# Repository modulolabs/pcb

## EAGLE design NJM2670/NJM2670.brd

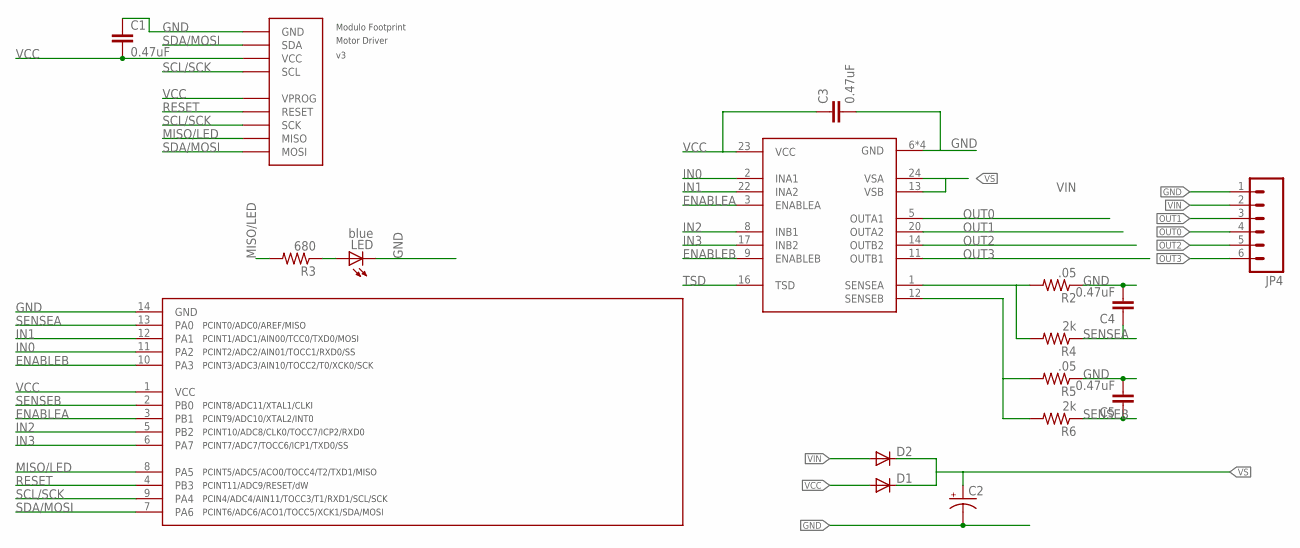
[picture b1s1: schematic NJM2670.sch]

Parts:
C1, C3, C4, C5: 0.47uF; 0805
C2: CAP_POLC; PANASONIC_C
D1, D2: DIODESMA; SMA-DIODE
JP4: M063.5MM-6; SCREWTERMINAL-3.5MM-6
LED: blue; CHIPLED_0805
R2, R5: .05; 0805
R3: 680; 0805
R4, R6: 2k; 0805
U$1: FOOTPRINTFOOTPRINT-2; FOOTPRINT2
U$3: TINY841; SOIC14
U$6: NJM2670; SOP-24-E3

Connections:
ENABLEA: U$3.3 (PB1), U$6.3 (ENABLEA)
ENABLEB: U$3.10 (PA3), U$6.9 (ENABLEB)
GND: C1.1, C2.-, C3.2, C4.2, C5.2, JP4.1, LED.C, R2.1, R5.1, U$1.BUS0 (GND), U$3.14 (GND), U$6.6 (GND), U$6.7 (GND), U$6.18 (GND), U$6.19 (GND)
IN0: U$3.11 (PA2), U$6.2 (INA1)
IN1: U$3.12 (PA1), U$6.22 (INA2)
IN2: U$3.5 (PB2), U$6.8 (INB1)
IN3: U$3.6 (PA7), U$6.17 (INB2)
MISO/LED: R3.2, U$1.PROG3 (MISO), U$3.8 (PA5)
unnamed: R2.2, R4.2, U$6.1 (SENSEA)
unnamed: R5.2, R6.2, U$6.12 (SENSEB)
unnamed: LED.A, R3.1
OUT0: JP4.4, U$6.5 (OUTA1)
OUT1: JP4.3, U$6.20 (OUTA2)
OUT2: JP4.5, U$6.14 (OUTB2)
OUT3: JP4.6, U$6.11 (OUTB1)
RESET: U$1.PROG1 (RESET), U$3.4 (PB3)
SCL/SCK: U$1.BUS3 (SCL), U$1.PROG2 (SCK), U$3.9 (PA4)
SDA/MOSI: U$1.BUS1 (SDA), U$1.PROG4 (MOSI), U$3.7 (PA6)
SENSEA: C4.1, R4.1, U$3.13 (PA0)
SENSEB: C5.1, R6.1, U$3.2 (PB0)
TSD: U$6.16 (TSD)
VCC: C1.2, C3.1, D1.A, U$1.BUS2 (VCC), U$1.PROG0 (VPROG), U$3.1 (VCC), U$6.23 (VCC)
VIN: D2.A, JP4.2
VS: C2.+, D1.C, D2.C, U$6.13 (VSB), U$6.24 (VSA)

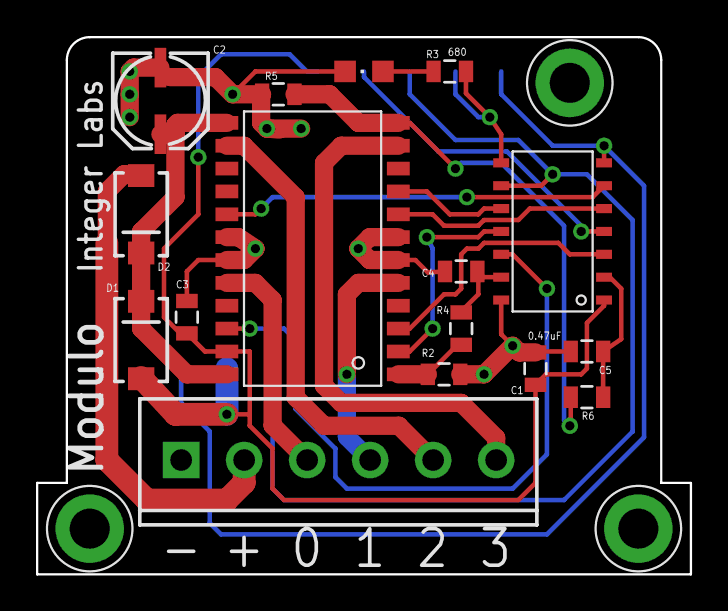
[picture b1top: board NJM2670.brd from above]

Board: 2 copper layers, 36.3 x 29.8 mm, 17 parts (0 on the bottom side), 23 nets.

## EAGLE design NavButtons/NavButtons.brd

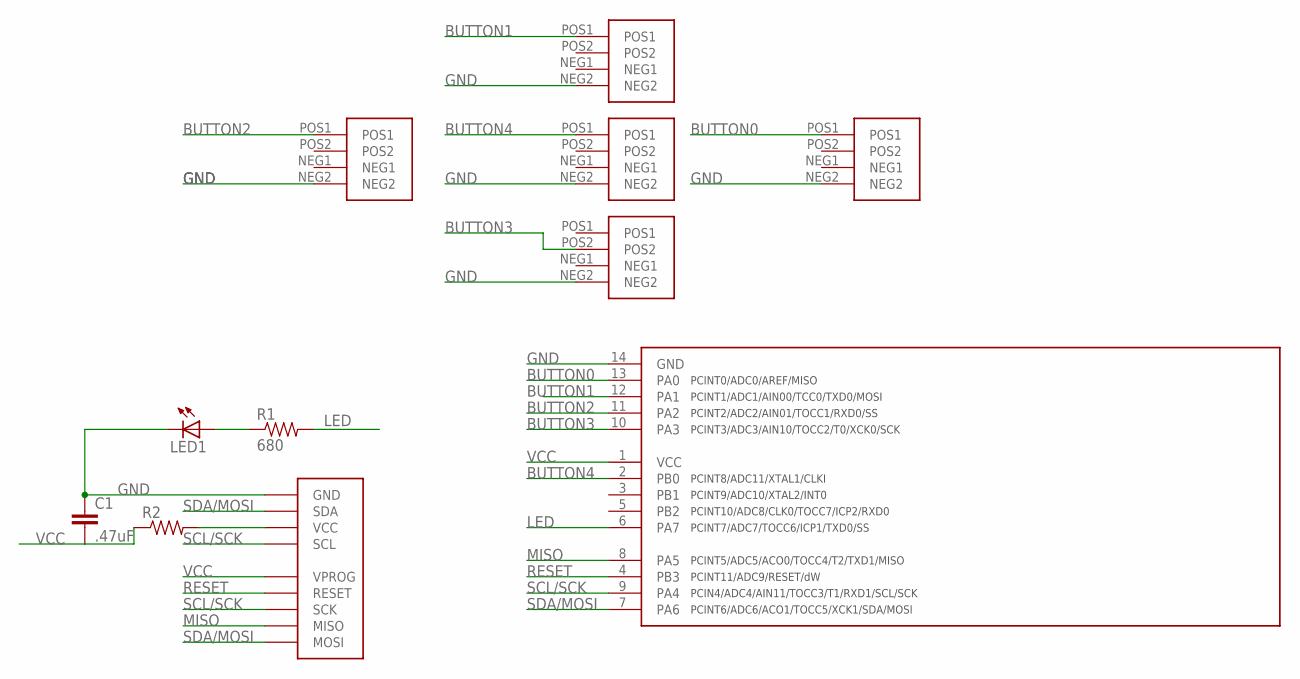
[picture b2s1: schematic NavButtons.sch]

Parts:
B1, B3, B4, B5, B7: TACT-SWITCH; MJTP1138
C1: .47uF; 0805
LED1: LEDCHIP-LED0805; CHIP-LED0805
R1: 680; 0805
R2: RESISTOR0805-RES; 0805
U$1: TINY841; SOIC14
U$2: FOOTPRINTFOOTPRINT-2; FOOTPRINT2

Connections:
BUTTON0: B5.POS1, U$1.13 (PA0)
BUTTON1: B1.POS1, U$1.12 (PA1)
BUTTON2: B3.POS1, U$1.11 (PA2)
BUTTON3: B7.POS2, U$1.10 (PA3)
BUTTON4: B4.POS1, U$1.2 (PB0)
GND: B1.NEG2, B3.NEG2, B4.NEG2, B5.NEG2, B7.NEG2, C1.1, LED1.C, U$1.14 (GND), U$2.BUS0 (GND)
LED: R1.2, U$1.6 (PA7)
MISO: U$1.8 (PA5), U$2.PROG3 (MISO)
unnamed: R2.2, U$2.BUS2 (VCC)
unnamed: LED1.A, R1.1
RESET: U$1.4 (PB3), U$2.PROG1 (RESET)
SCL/SCK: U$1.9 (PA4), U$2.BUS3 (SCL), U$2.PROG2 (SCK)
SDA/MOSI: U$1.7 (PA6), U$2.BUS1 (SDA), U$2.PROG4 (MOSI)
VCC: C1.2, R2.1, U$1.1 (VCC), U$2.PROG0 (VPROG)

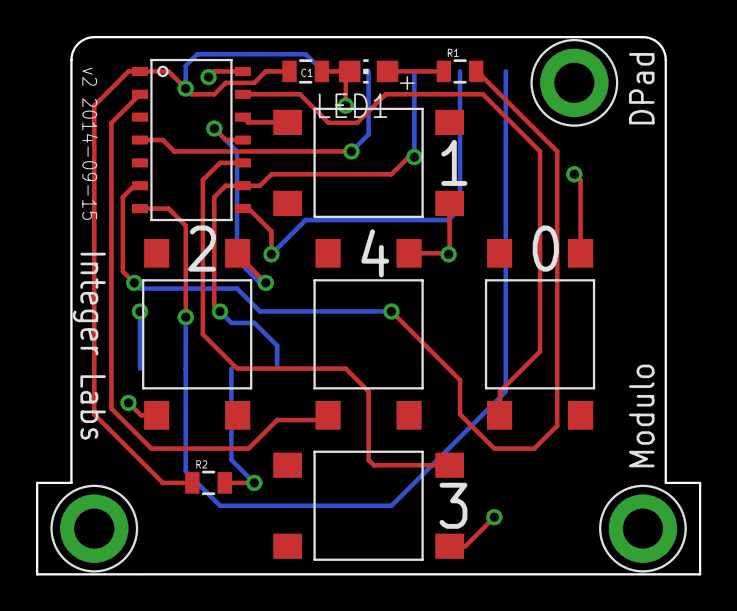
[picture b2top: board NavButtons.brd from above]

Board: 2 copper layers, 36.8 x 29.8 mm, 11 parts (0 on the bottom side), 14 nets.

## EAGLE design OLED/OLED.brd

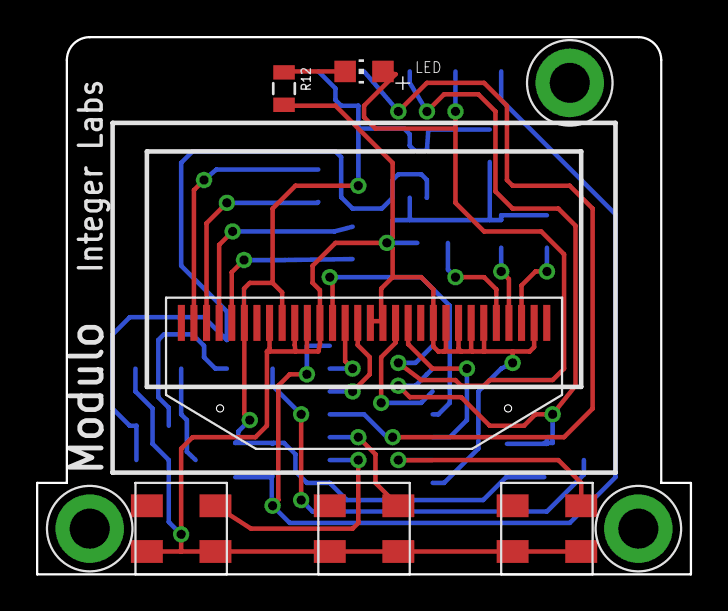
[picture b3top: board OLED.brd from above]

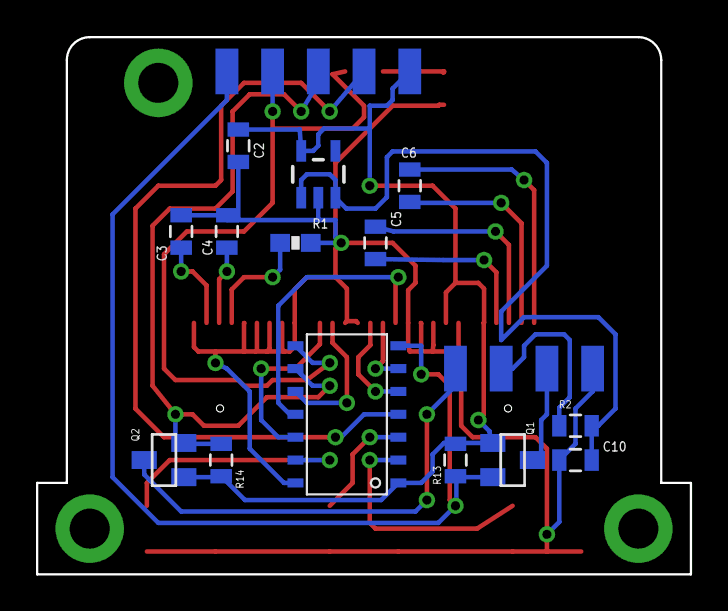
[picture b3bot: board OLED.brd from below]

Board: 2 copper layers, 36.3 x 29.8 mm, 21 parts (14 on the bottom side), 26 nets.

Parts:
C2, C10: .47uF; 0805
C3, C4: 2.2uF; 0805
C5, C6: 1uF; 0805
LED: blue; CHIP-LED0805
Q1, Q2: MOSFET-NCHANNELBSS138; SOT23
R1: 390k; 0603-RES
R2: 1; 0805
R12: 680; 0805
R13, R14: 2k; 0805
U$1: OLEDREVERSE; FPC-30-REVERSE
U$2: 3.3V/150mA; SOT23-5
U$3: TINY841; SOIC14
U$4: FOOTPRINTFOOTPRINT-2; FOOTPRINT2
U$5, U$6, U$7: TACT-SWITCHBOURNS-7914J; BOURNS-7914J

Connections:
+3.3V: C2.2, Q1.1, Q2.1, R13.2, R14.2, U$1.6, U$1.9, U$2.5, U$3.1, U$4.PROG0
+5V: C10.2, R2.1, U$2.1, U$2.3
BUTTON1: U$3.2, U$5.POS$1
BUTTON2: U$3.3, U$6.POS$1
BUTTON3: U$3.13, U$7.POS$1
DISPLAY_CS: U$1.13, U$3.11
DISPLAY_D/C: U$1.15, U$3.5
DISPLAY_MOSI: U$1.19, U$3.12
DISPLAY_RESET: U$1.14, U$3.6
DISPLAY_SCK: U$1.18, U$3.10
GND: C2.1, C3.2, C4.2, C10.1, R1.1, R12.1, U$1.8, U$1.10, U$1.11, U$1.12, U$1.16, U$1.17, U$1.21, U$1.22, U$1.23, U$1.24, U$1.25, U$1.29, U$2.2, U$3.14, U$4.BUS0, U$5.NEG$1, U$5.NEG$2, U$6.NEG$1, U$6.NEG$2, U$7.NEG$1, U$7.NEG$2
MISO/LED: LED.A, U$3.8, U$4.PROG3
unnamed: R1.2, U$1.26
unnamed: R2.2, U$4.BUS2
unnamed: C3.1, U$1.28
unnamed: C4.1, U$1.27
unnamed: LED.C, R12.2
unnamed: C5.2, U$1.4
unnamed: C6.2, U$1.2
unnamed: C5.1, U$1.5
unnamed: C6.1, U$1.3
RESET: U$3.4, U$4.PROG1
SCL3.3/SCK: Q2.2, R14.1, U$3.9, U$4.PROG2
SCL5: Q2.3, U$4.BUS3
SDA3.3/MOSI: Q1.2, R13.1, U$3.7, U$4.PROG4
SDA5: Q1.3, U$4.BUS1

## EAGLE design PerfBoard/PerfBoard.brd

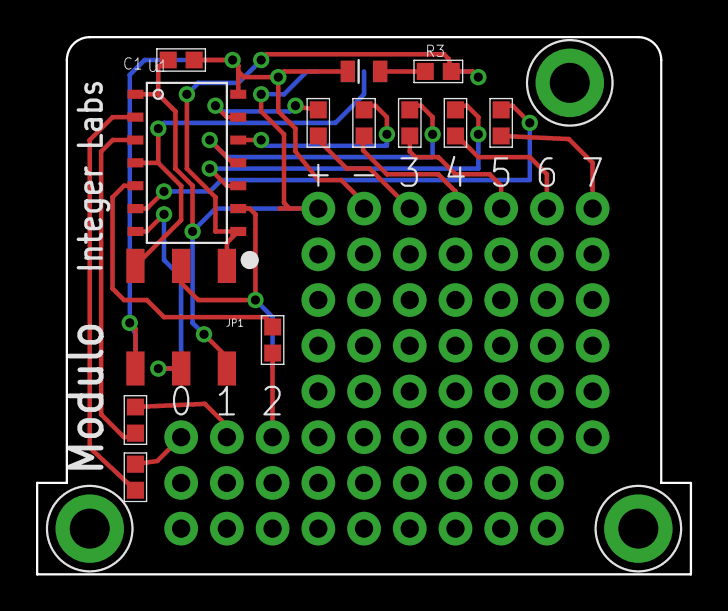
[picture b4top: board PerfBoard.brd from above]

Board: 2 copper layers, 36.3 x 29.8 mm, 31 parts (0 on the bottom side), 23 nets.

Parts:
C1: 100nF; 0603
JP1: 2X3_SMD
JP2, JP5, JP8, JP9, JP12, JP13: 1X05_NO_SILK
JP3, JP4, JP6, JP7, JP10, JP11, JP14, JP15, JP16, JP17, JP18: 1X03_NO_SILK
LED1: blue; 0805-LED
PCB1: EXCLUDE; FOOTPRINT2
R1, R2, R4, R5, R6, R7, R8, R9: 150Ω; 0603
R3: 681Ω; 0603
U1: ATTINY841; SOIC-14

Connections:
A0: R4.1, U1.13
A1: R6.1, U1.12
A2: R8.1, U1.11
A3: R5.1, U1.10
A7: R7.1, U1.6
B0: R9.1, U1.2
B1: R2.1, U1.3
B2: R1.1, U1.5
GND: C1.1, JP1.6, JP7.1, LED1.C, PCB1.BUS0, U1.14
LED/MISO: JP1.1, PCB1.PROG3, R3.2, U1.8
unnamed: LED1.A, R3.1
unnamed: JP3.1, R1.2
unnamed: JP6.1, R2.2
unnamed: JP10.1, R4.2
unnamed: JP11.1, R5.2
unnamed: JP15.1, R7.2
unnamed: JP14.1, R6.2
unnamed: JP16.1, R8.2
unnamed: JP17.1, R9.2
RESET: JP1.5, PCB1.PROG1, U1.4
SCL/SCK: JP1.3, PCB1.BUS3, U1.9
SDA/MOSI: JP1.4, PCB1.BUS1, U1.7
VCC: C1.2, JP1.2, JP4.1, PCB1.BUS2, PCB1.PROG0, U1.1

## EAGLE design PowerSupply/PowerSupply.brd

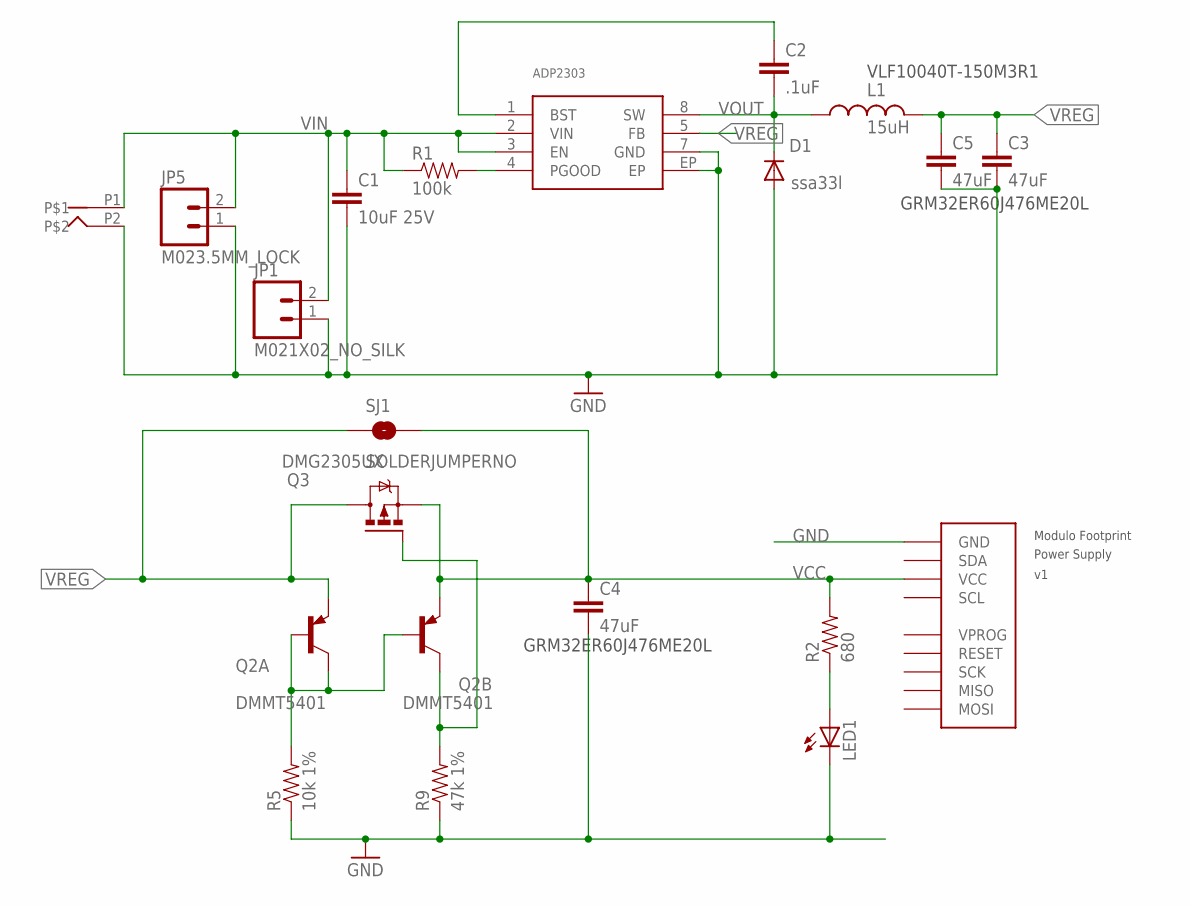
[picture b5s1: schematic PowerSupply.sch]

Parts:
C1: 10uF 25V; 0805
C2: .1uF; 0805
C3, C4, C5: 47uF; 1210
D1: ssa33l; SMA-DIODE
JP1: M021X02_NO_SILK; 1X02_NO_SILK
JP5: M023.5MM_LOCK; SCREWTERMINAL-3.5MM-2_LOCK
L1: 15uH; INDUCTOR-VLF10040
LED1: LEDCHIPLED_0805; CHIPLED_0805
Q2: DMMT5401; SOT-26
Q3: DMG2305UX; MICRO3
R1: 100k; 0805
R2: 680; 0805
R5: 10k 1%; 0805
R9: 47k 1%; 0805
SJ1: SOLDERJUMPERNO; SJ_2S-NO
U$3: ADP2303; SOIC8-EP
U$4: FOOTPRINTFOOTPRINT-2; FOOTPRINT2
U$21: DC-JACK; DC-POWER-JACK

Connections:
GND: C1.2, C3.2, C4.2, C5.2, D1.A, JP1.1, JP5.1, LED1.C, R5.1, R9.1, U$3.7 (GND), U$3.EP, U$4.BUS0 (GND), U$21.P2
unnamed: R1.2, U$3.4 (PGOOD)
unnamed: LED1.A, R2.1
unnamed: C2.1, U$3.1 (BST)
unnamed: Q2.1 (C), Q2.2 (B), Q2.3 (B), R5.2
unnamed: Q2.4 (C), Q3.1 (G), R9.2
VCC: C4.1, Q2.5 (E), Q3.2 (S), R2.2, SJ1.2, U$4.BUS2 (VCC)
VIN: C1.1, JP1.2, JP5.2, R1.1, U$3.2 (VIN), U$3.3 (EN), U$21.P1
VOUT: C2.2, D1.C, L1.P$1 (1), U$3.8 (SW)
VREG: C3.1, C5.1, L1.P$2 (2), Q2.6 (E), Q3.3 (D), SJ1.1, U$3.5 (FB)

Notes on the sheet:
GRM32ER60J476ME20L
VLF10040T-150M3R1

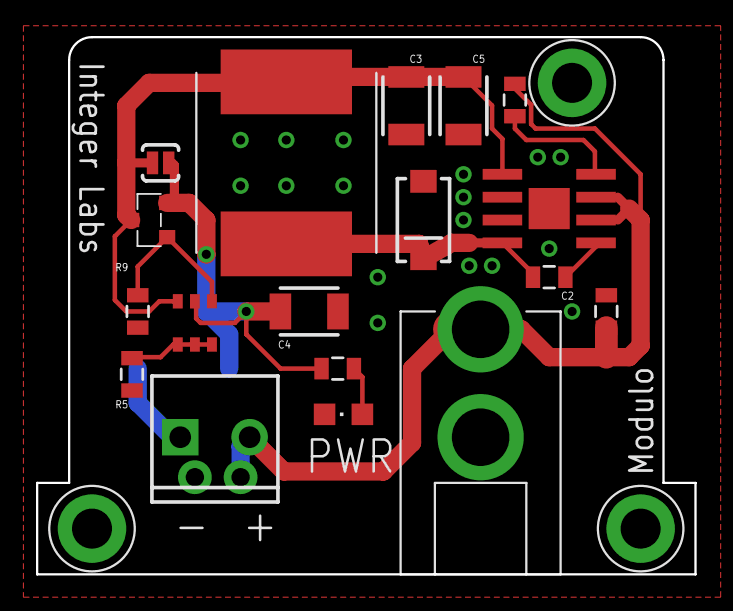
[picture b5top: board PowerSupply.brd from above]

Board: 2 copper layers, 36.6 x 29.8 mm, 20 parts (0 on the bottom side), 10 nets.

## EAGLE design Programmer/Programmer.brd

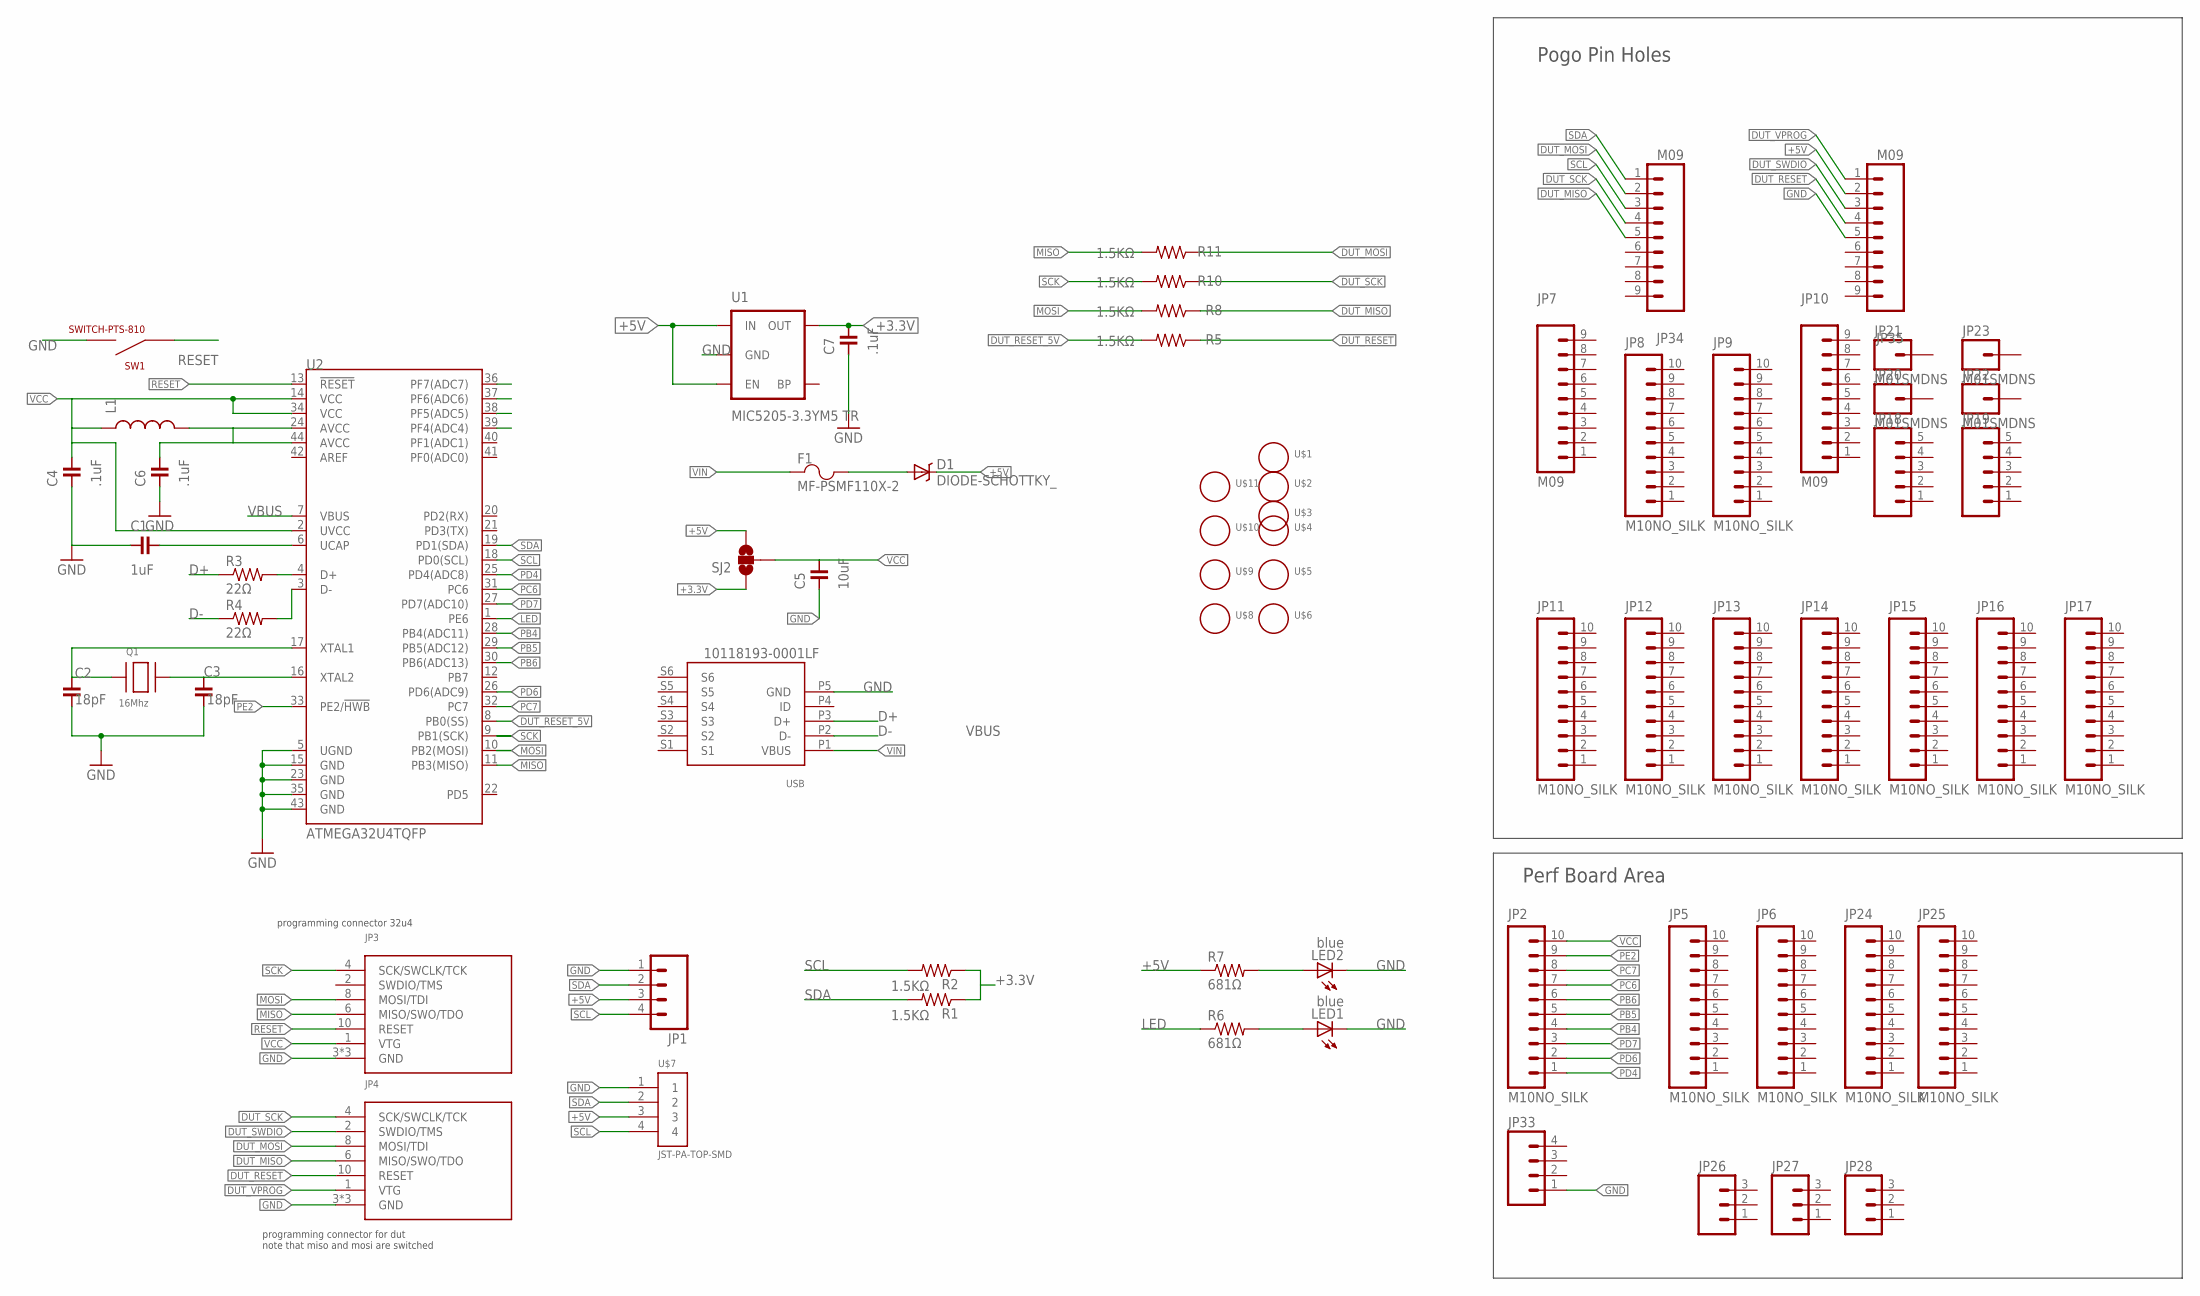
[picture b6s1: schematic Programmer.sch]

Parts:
C1: 1uF; 0603
C2, C3: 18pF; 0603
C4, C6, C7: .1uF; 0603
C5: 10uF; 0603
D1: DIODE-SCHOTTKY_; SMA-DIODE
F1: MF-PSMF110X-2; 0805; PARTNUM MF-PSFM110X-2
JP1: M04LOCK; 1X04_LOCK
JP2, JP5, JP6, JP8, JP9, JP11, JP12, JP13, JP14, JP15, JP16, JP17, JP24, JP25: M10NO_SILK; 1X10_NO_SILK
JP3, JP4: ICSP; 2X5-.05
JP7, JP10, JP34, JP35: M09; 1X09
JP18, JP19: M05NO_SILK; 1X05_NO_SILK
JP20, JP21, JP22, JP23: M01SMDNS; 1X01NS
JP26, JP27, JP28: M031X03_NO_SILK; 1X03_NO_SILK
JP33: M041X04_NO_SILK; 1X04_NO_SILK
L1: INDUCTOR0805; 0805
LED1, LED2: blue; 0805-LED
Q1: 16Mhz; NX3225; PARTNUM CX3225GB16000D0HEQCC
R1, R2, R5, R8, R10, R11: 1.5KΩ; 0603
R3, R4: 22Ω; 0603
R6, R7: 681Ω; 0603
SJ2: SOLDERJUMPER_2WAYPASTE1&2; SJ_3_PASTE1&2
SW1: SWITCH-PTS-810; TACT-SWITCH-PTS-810
U1: MIC5205-3.3YM5 TR; SOT23-5; PARTNUM MIC5205-3.3YM5 TR
U2: ATMEGA32U4TQFP; SPARKFUN-DIGITALIC_TQFP44; PARTNUM ATMEGA32U4TQFP
U3: USBFCI-MICROB; USB-MICROB-FCI; PARTNUM 10118193-0001LF
U$1, U$2, U$3, U$4, U$5, U$6, U$8, U$9, U$10, U$11: HOLE#2; HOLE-#2
U$7: JST-PA-TOP-SMD

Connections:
+3.3V: C7.1, R1.1, R2.1, SJ2.1, U1.5 (OUT)
+5V: D1.C, JP1.3, JP35.2, R7.1, SJ2.3, U1.1 (IN), U1.3 (EN), U$7.3
D+: R3.1, U3.P3 (D+)
D-: R4.1, U3.P2 (D-)
DUT_MISO: JP4.6 (MISO/SWO/TDO), JP34.5, R8.1
DUT_MOSI: JP4.8 (MOSI/TDI), JP34.2, R11.1
DUT_RESET: JP4.10 (RESET), JP35.4, R5.1
DUT_RESET_5V: R5.2, U2.8 (PB0(SS))
DUT_SCK: JP4.4 (SCK/SWCLK/TCK), JP34.4, R10.1
DUT_SWDIO: JP4.2 (SWDIO/TMS), JP35.3
DUT_VPROG: JP4.1 (VTG), JP35.1
GND: C1.2, C2.2, C3.2, C4.2, C5.2, C6.2, C7.2, JP1.1, JP3.3 (GND), JP3.5 (GND), JP3.9 (GND), JP4.3 (GND), JP4.5 (GND), JP4.9 (GND), JP33.1, JP35.5, LED1.C, LED2.C, SW1.P$3 (NEG1), SW1.P$4 (NEG1), U1.2 (GND), U2.5 (UGND), U2.15 (GND), U2.23 (GND), U2.35 (GND), U2.43 (GND), U3.P5 (GND), U$7.1
LED: R6.1, U2.1 (PE6)
MISO: JP3.6 (MISO/SWO/TDO), R11.2, U2.11 (PB3(MISO))
MOSI: JP3.8 (MOSI/TDI), R8.2, U2.10 (PB2(MOSI))
unnamed: C1.1, U2.6 (UCAP)
unnamed: C6.1, L1.2, U2.24 (AVCC), U2.44 (AVCC)
unnamed: C3.1, Q1.3 (X2), U2.16 (XTAL2)
unnamed: LED1.A, R6.2
unnamed: R3.2, U2.4 (D+)
unnamed: R4.2, U2.3 (D-)
unnamed: LED2.A, R7.2
unnamed: C2.1, Q1.1 (X1), U2.17 (XTAL1)
PB4: JP2.4, U2.28 (PB4(ADC11))
PB5: JP2.5, U2.29 (PB5(ADC12))
PB6: JP2.6, U2.30 (PB6(ADC13))
PC6: JP2.7, U2.31 (PC6)
PC7: JP2.8, U2.32 (PC7)
PD4: JP2.1, U2.25 (PD4(ADC8))
PD6: JP2.2, U2.26 (PD6(ADC9))
PD7: JP2.3, U2.27 (PD7(ADC10))
PE2: JP2.9, U2.33 (PE2/!HWB)
RESET: JP3.10 (RESET), SW1.P$1 (POS1), SW1.P$2 (POS1), U2.13 (!RESET)
SCK: JP3.4 (SCK/SWCLK/TCK), R10.2, U2.9 (PB1(SCK))
SCL: JP1.4, JP34.3, R2.2, U2.18 (PD0(SCL)), U$7.4
SDA: JP1.2, JP34.1, R1.2, U2.19 (PD1(SDA)), U$7.2
VBUS: D1.A, F1.2, U2.7 (VBUS)
VCC: C4.1, C5.1, JP2.10, JP3.1 (VTG), L1.1, SJ2.2, U2.2 (UVCC), U2.14 (VCC), U2.34 (VCC)
VIN: F1.1, U3.P1 (VBUS)

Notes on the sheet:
programming connector 32u4
programming connector for dut note that miso and mosi are switched
Pogo Pin Holes
Perf Board Area

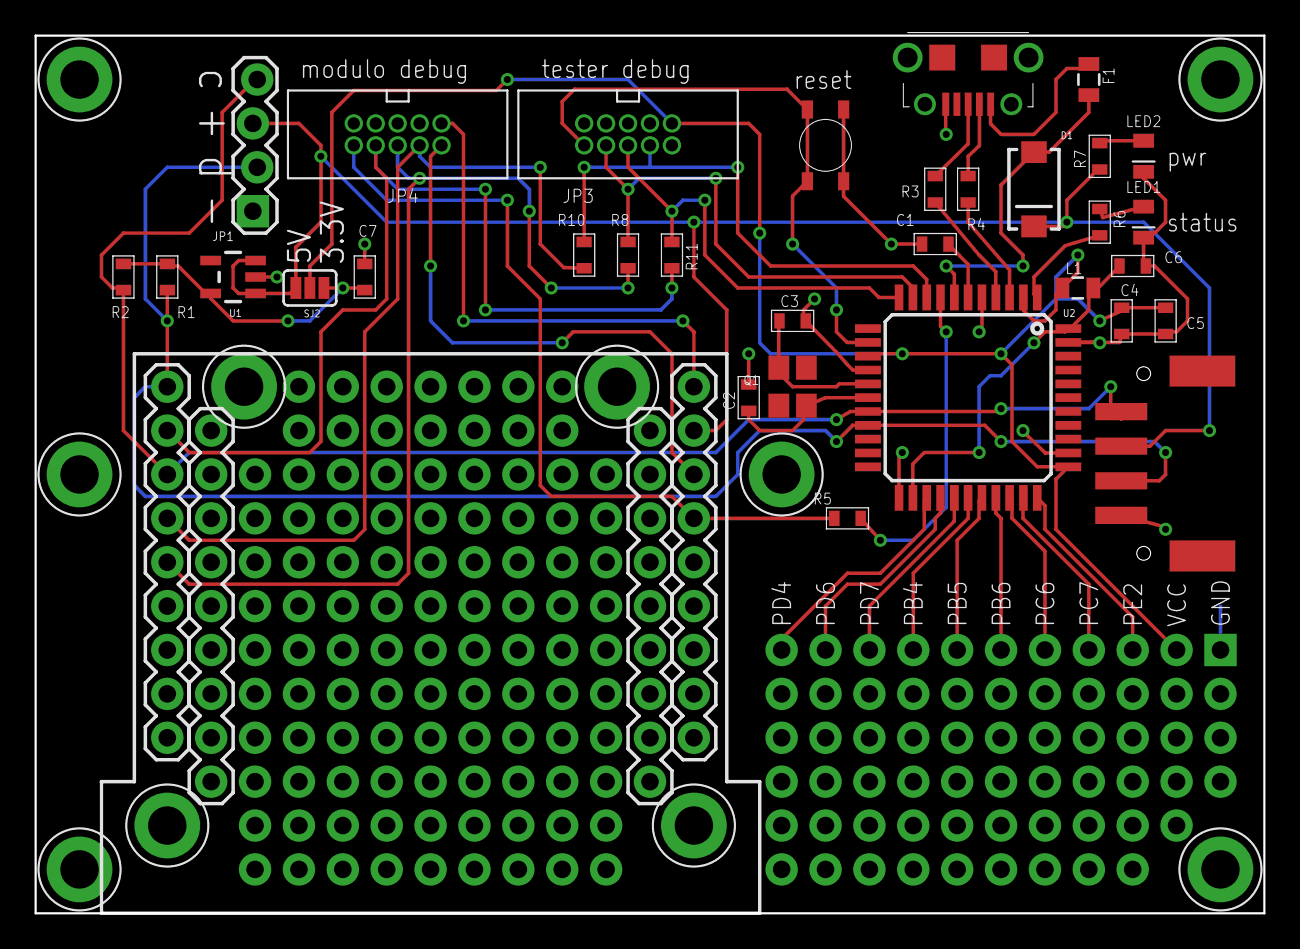
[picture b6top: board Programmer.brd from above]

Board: 2 copper layers, 71.1 x 50.8 mm, 70 parts (0 on the bottom side), 39 nets.

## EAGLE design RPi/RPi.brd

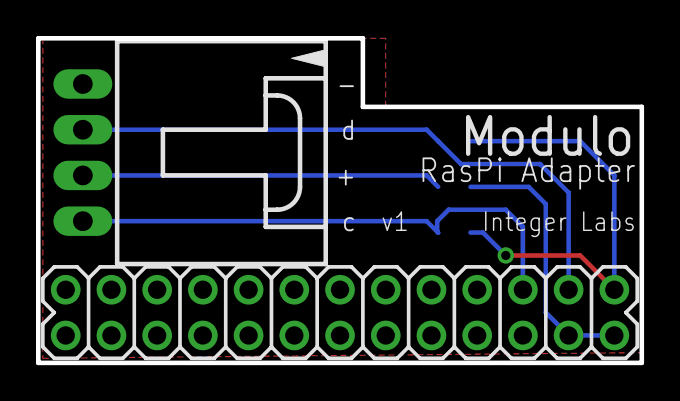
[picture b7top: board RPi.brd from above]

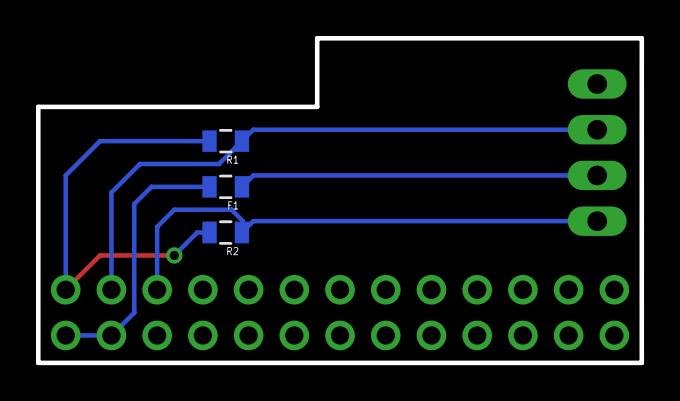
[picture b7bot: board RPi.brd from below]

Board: 2 copper layers, 33.5 x 18.0 mm, 5 parts (3 on the bottom side), 6 nets.

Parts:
F1: MF-PSMF010X-2; 0805
R1, R2: 0805
U$2: M13X22X13; 2X13
X1: C-GRID-04-70553; 70553-04

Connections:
3.3V: R1.2, R2.2, U$2.1
5V: F1.1, X1.3
GND: U$2.6, X1.1
unnamed: F1.2, U$2.2, U$2.4
SCL: R2.1, U$2.5, X1.4
SDA: R1.1, U$2.3, X1.2

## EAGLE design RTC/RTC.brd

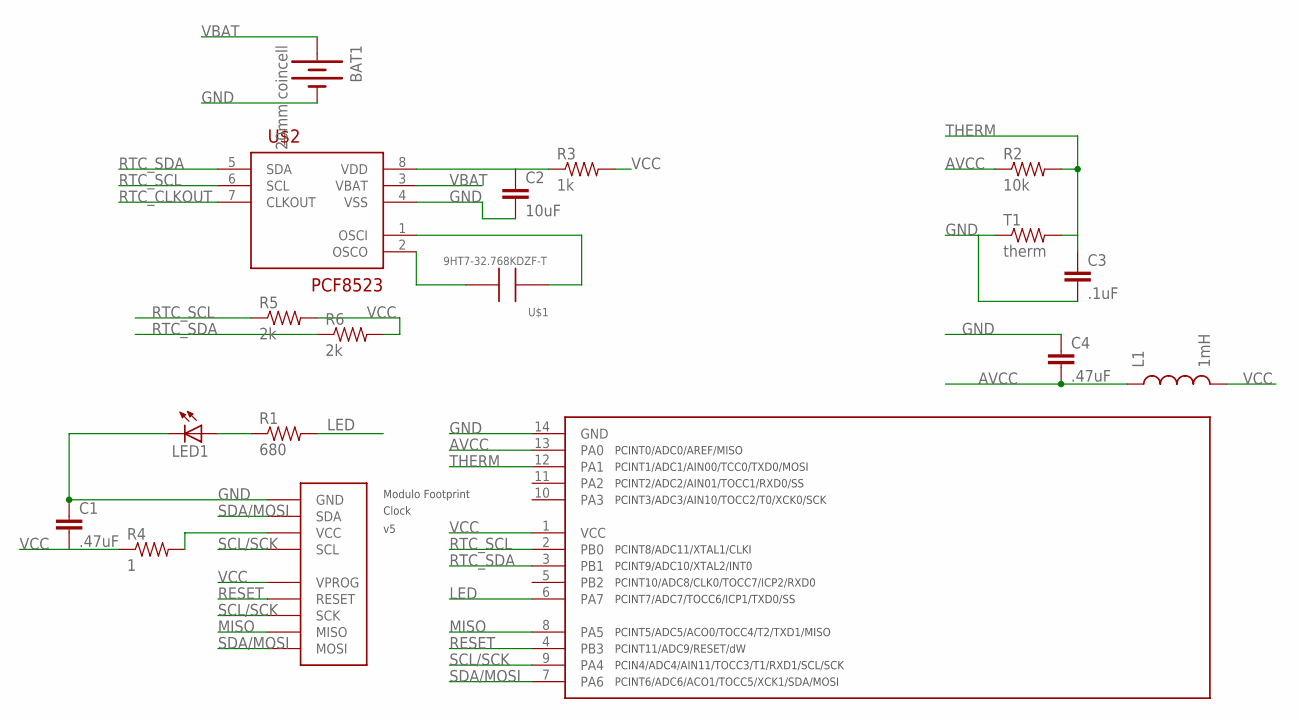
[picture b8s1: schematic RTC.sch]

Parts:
BAT1: 20mm coincell; BATTCON_20MM_4LEGS
C1, C4: .47uF; 0805
C2: 10uF; 0805
C3: .1uF; 0805
L1: 1mH; 1007
LED1: LEDCHIP-LED0805; CHIP-LED0805
R1: 680; 0805
R2: 10k; 0805
R3: 1k; 0805
R4: 1; 0805
R5, R6: 2k; 0805
T1: therm; 0805
U$1: 9HT7-32.768KDZF-T; CRYSTAL-ABS25
U$2: PCF8523; SOIC-8
U$3: TINY841; SOIC14
U$4: FOOTPRINTFOOTPRINT-2; FOOTPRINT2

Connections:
AVCC: C4.2, L1.1, R2.1, U$3.13 (PA0)
GND: BAT1.2 (-), C1.1, C2.2, C3.2, C4.1, LED1.C, T1.1, U$2.4 (VSS), U$3.14 (GND), U$4.BUS0 (GND)
LED: R1.2, U$3.6 (PA7)
MISO: U$3.8 (PA5), U$4.PROG3 (MISO)
unnamed: R4.2, U$4.BUS2 (VCC)
unnamed: C2.1, R3.1, U$2.8 (VDD)
unnamed: U$1.P$1, U$2.1 (OSCI)
unnamed: LED1.A, R1.1
unnamed: U$1.P$4, U$2.2 (OSCO)
RESET: U$3.4 (PB3), U$4.PROG1 (RESET)
RTC_CLKOUT: U$2.7 (CLKOUT)
RTC_SCL: R5.1, U$2.6 (SCL), U$3.2 (PB0)
RTC_SDA: R6.1, U$2.5 (SDA), U$3.3 (PB1)
SCL/SCK: U$3.9 (PA4), U$4.BUS3 (SCL), U$4.PROG2 (SCK)
SDA/MOSI: U$3.7 (PA6), U$4.BUS1 (SDA), U$4.PROG4 (MOSI)
THERM: C3.1, R2.2, T1.2, U$3.12 (PA1)
VBAT: BAT1.1 (+), U$2.3 (VBAT)
VCC: C1.2, L1.2, R3.2, R4.1, R5.2, R6.2, U$3.1 (VCC), U$4.PROG0 (VPROG)

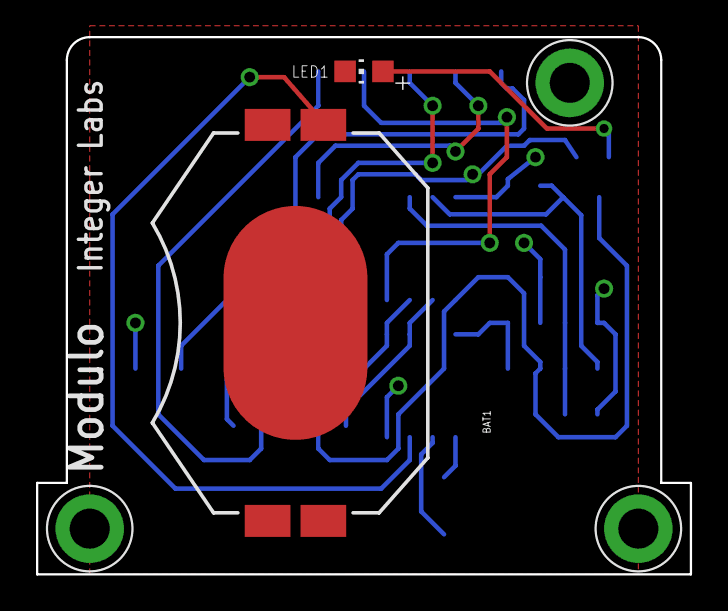
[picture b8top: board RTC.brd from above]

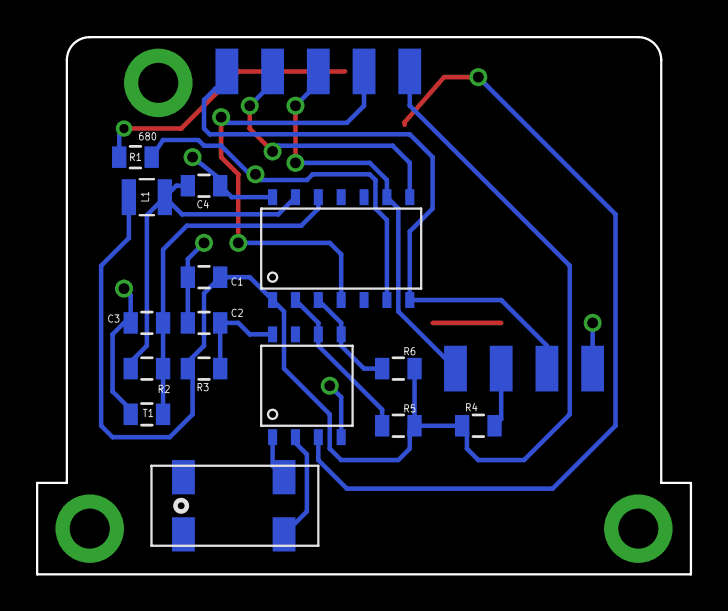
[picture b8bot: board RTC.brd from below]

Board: 2 copper layers, 36.3 x 29.8 mm, 18 parts (15 on the bottom side), 17 nets.

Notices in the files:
parts and their libraries:
SparkFun-Capacitors: Licensing: Creative Commons ShareAlike 4.0 International - https://creativecommons.org/licenses/by-sa/4.0
